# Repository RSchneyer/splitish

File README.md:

# splitish
My first attempt at designing a mechanical keyboard. Split-ish 4x12 ortholinear layout designed for Kailh Choc switches. Rev 1 works, but is far from perfect, so order at your own risk.

version 2 now exists, but I haven't had it fabricated though. Should still work.

Firmware can be found [here](hhttps://github.com/qmk/qmk_firmware/tree/master/keyboards/splitish)
___
Made with lots of help from [Ai03's PCB design guide](https://wiki.ai03.me/books/pcb-design)

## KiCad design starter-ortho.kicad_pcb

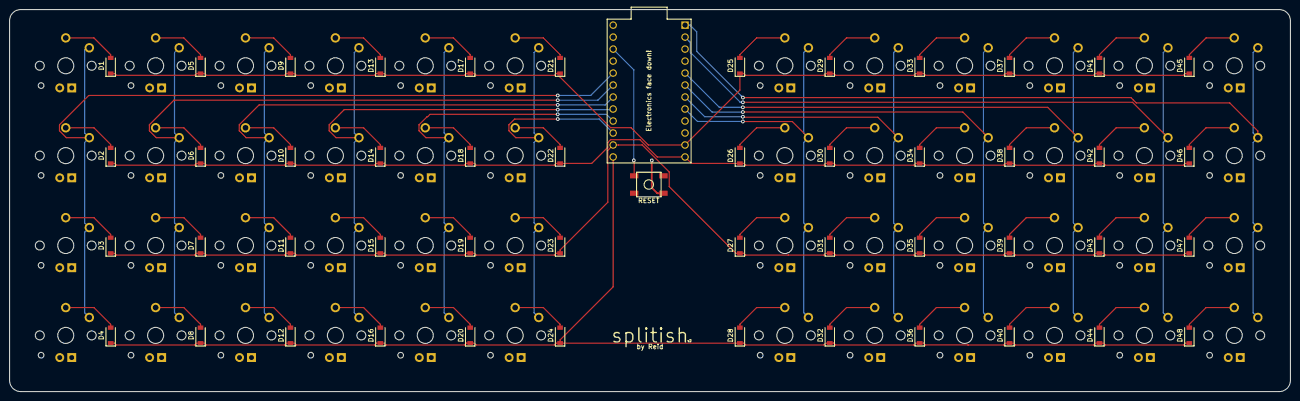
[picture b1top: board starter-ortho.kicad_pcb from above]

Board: 2 copper layers, 271.5 x 81.0 mm, 98 parts (1 on the bottom side), 66 nets.

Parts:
D1, D2, D3, D4, D5, D6, D7, D8, D9, D10, D11, D12, D13, D14, D15, D16, D17, D18, D19, D20, D21, D22, D23, D24, D25, D26, D27, D28, D29, D30, D31, D32, D33, D34, D35, D36, D37, D38, D39, D40, D41, D42, D43, D44, D45, D46, D47, D48: D_Small; D_SOD-123
MX1, MX2, MX3, MX4, MX5, MX6, MX7, MX8, MX9, MX10, MX11, MX12, MX13, MX14, MX15, MX16, MX17, MX18, MX19, MX20, MX21, MX22, MX23, MX24, MX25, MX26, MX27, MX28, MX29, MX30, MX31, MX32, MX33, MX34, MX35, MX36, MX37, MX38, MX39, MX40, MX41, MX42, MX43, MX44, MX45, MX46, MX47, MX48: MX-NoLED; KailhChoc-1U
RESET: SW_Push; SKQG-1155865
U1: ProMicro

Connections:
COL0: MX1.1, MX2.1, MX3.1, MX4.1, U1.20
COL1: MX5.1, MX6.1, MX7.1, MX8.1, U1.19
COL2: MX9.1, MX10.1, MX11.1, MX12.1, U1.18
COL3: MX13.1, MX14.1, MX15.1, MX16.1, U1.17
COL4: MX17.1, MX18.1, MX19.1, MX20.1, U1.16
COL5: MX21.1, MX22.1, MX23.1, MX24.1, U1.15
COL6: MX25.1, MX26.1, MX27.1, MX28.1, U1.8
COL7: MX29.1, MX30.1, MX31.1, MX32.1, U1.7
COL8: MX33.1, MX34.1, MX35.1, MX36.1, U1.6
COL9: MX37.1, MX38.1, MX39.1, MX40.1, U1.5
COL10: MX41.1, MX42.1, MX43.1, MX44.1, U1.2
COL11: MX45.1, MX46.1, MX47.1, MX48.1, U1.1
GND: RESET.2, U1.3, U1.4, U1.23
unnamed: D1.2, MX1.2
unnamed: D2.2, MX2.2
unnamed: D3.2, MX3.2
unnamed: D4.2, MX4.2
unnamed: D5.2, MX5.2
unnamed: D6.2, MX6.2
unnamed: D7.2, MX7.2
unnamed: D8.2, MX8.2
unnamed: D9.2, MX9.2
unnamed: D10.2, MX10.2
unnamed: D11.2, MX11.2
unnamed: D12.2, MX12.2
unnamed: D13.2, MX13.2
unnamed: D14.2, MX14.2
unnamed: D15.2, MX15.2
unnamed: D16.2, MX16.2
unnamed: D17.2, MX17.2
unnamed: D18.2, MX18.2
unnamed: D19.2, MX19.2
unnamed: D20.2, MX20.2
unnamed: D21.2, MX21.2
unnamed: D22.2, MX22.2
unnamed: D23.2, MX23.2
unnamed: D24.2, MX24.2
unnamed: D25.2, MX25.2
unnamed: D26.2, MX26.2
unnamed: D27.2, MX27.2
unnamed: D28.2, MX28.2
unnamed: D29.2, MX29.2
unnamed: D30.2, MX30.2
unnamed: D31.2, MX31.2
unnamed: D32.2, MX32.2
unnamed: D33.2, MX33.2
unnamed: D34.2, MX34.2
unnamed: D35.2, MX35.2
unnamed: D36.2, MX36.2
unnamed: D37.2, MX37.2
unnamed: D38.2, MX38.2
unnamed: D39.2, MX39.2
unnamed: D40.2, MX40.2
unnamed: D41.2, MX41.2
unnamed: D42.2, MX42.2
unnamed: D43.2, MX43.2
unnamed: D44.2, MX44.2
unnamed: D45.2, MX45.2
unnamed: D46.2, MX46.2
unnamed: D47.2, MX47.2
unnamed: D48.2, MX48.2
unnamed: RESET.1, U1.22
ROW0: D1.1, D5.1, D9.1, D13.1, D17.1, D21.1, D25.1, D29.1, D33.1, D37.1, D41.1, D45.1, U1.11
ROW1: D2.1, D6.1, D10.1, D14.1, D18.1, D22.1, D26.1, D30.1, D34.1, D38.1, D42.1, D46.1, U1.12
ROW2: D3.1, D7.1, D11.1, D15.1, D19.1, D23.1, D27.1, D31.1, D35.1, D39.1, D43.1, D47.1, U1.14
ROW3: D4.1, D8.1, D12.1, D16.1, D20.1, D24.1, D28.1, D32.1, D36.1, D40.1, D44.1, D48.1, U1.13

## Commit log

2019-12-16 Inital Commit
2019-12-16 Added submodule library files
2019-12-16 Added libraries
2019-12-16 schematic complete
2019-12-16 created PCB layout
2019-12-16 Added edges and M2 holes
2019-12-16 Routed traces (poorly)
2019-12-16 undid edge cuts
2019-12-16 we're doing choc switches now baby
2019-12-16 all traces routed
    done well? we'll see...
2019-12-16 PCB done?
2019-12-16 removed name from silkscreen
2019-12-16 add images
2019-12-16 Updated README with images
2019-12-16 generated gerber files
2019-12-16 added zip file to gitignore
2019-12-16 re-added silkscreen
2020-01-17 Added silkscreen text for promicro (and other updates)
2020-01-17 Fixing DRC errors
2020-01-17 Regenerated gerber files and zipped them
2020-04-09 updated readme with photo of assembled board
2020-04-10 another readme update
2020-07-04 created splitish v2
2020-07-04 created and zipped v2 gerbers
2020-07-06 Updated README with correct firmware link
2020-07-06 deleted unused traces and remade gerbers
2020-10-20 Added assembly docs
2020-10-20 Quick update to assembly docs
